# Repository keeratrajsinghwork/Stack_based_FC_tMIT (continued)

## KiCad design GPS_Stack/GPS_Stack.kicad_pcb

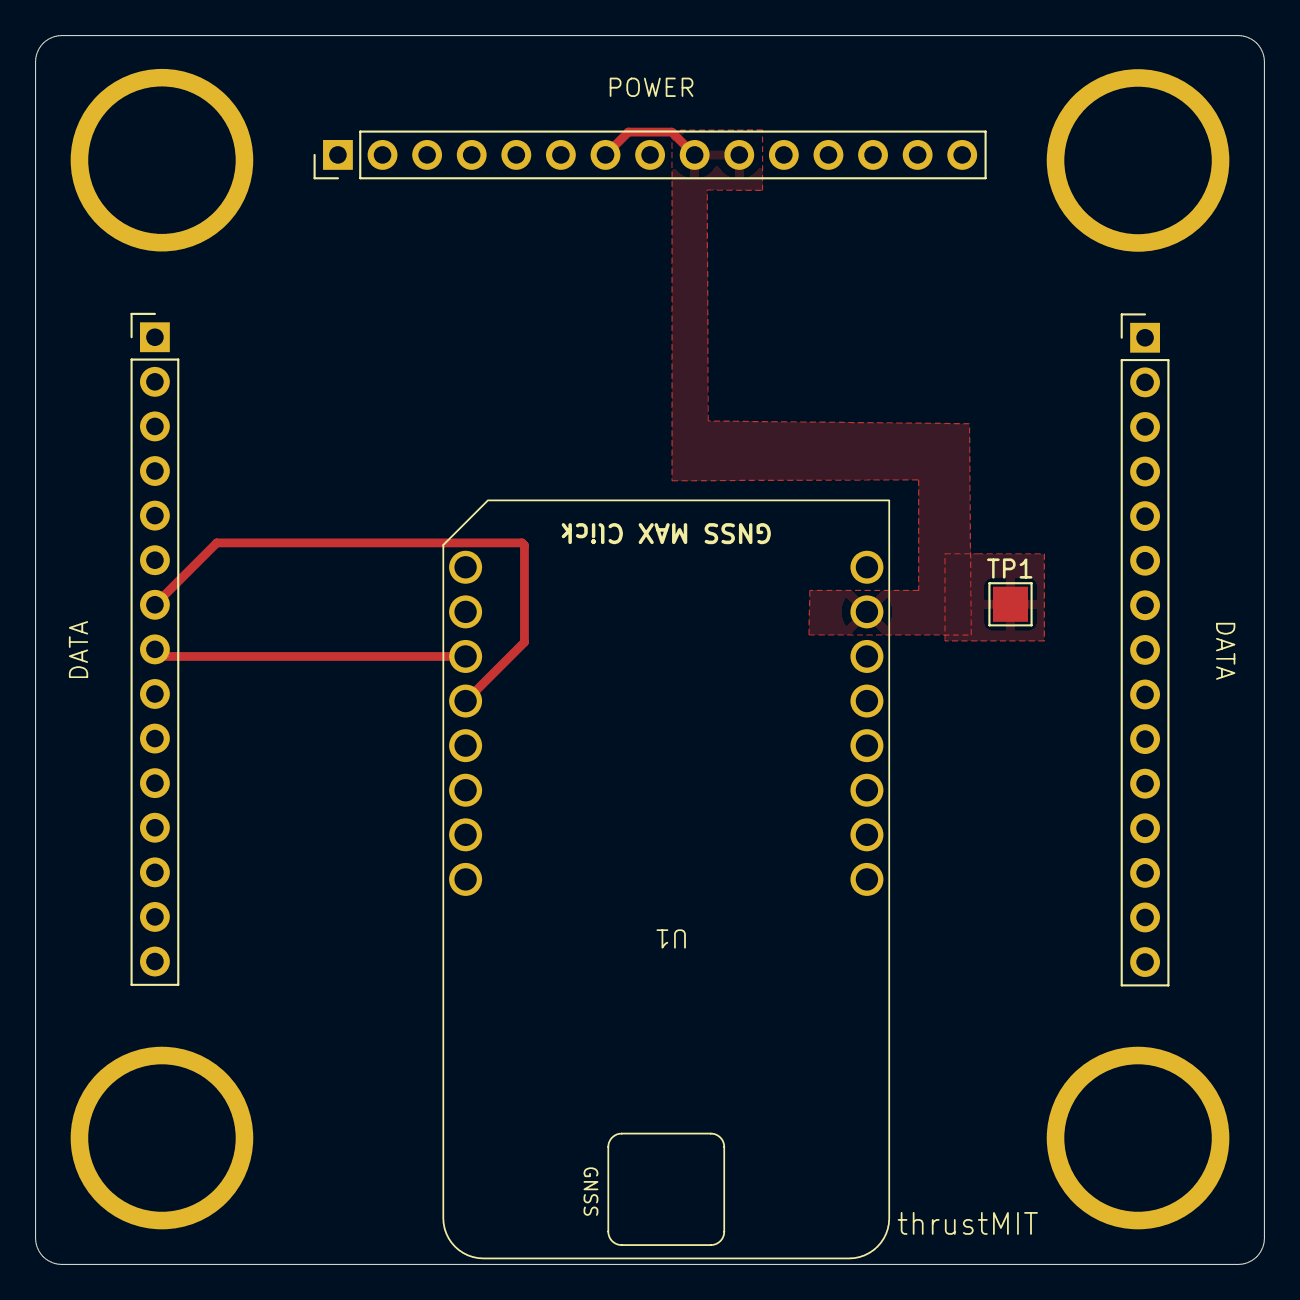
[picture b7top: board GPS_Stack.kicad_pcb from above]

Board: 2 copper layers, 70.0 x 70.0 mm, 3 parts (0 on the bottom side), 4 nets.

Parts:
TP1: TestPoint_Probe; TestPoint_Pad_2.0x2.0mm
U1: Mikroe_GNSS_MAX_CLICK_ThrustMIT
U2: FC_Stack_template

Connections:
3.3V: TP1.1, U1.2 (+3V3), U2.37, U2.39, U2.40
GND: U1.1 (GND), U1.9 (GND), U2.49 (1), U2.50 (1), U2.51 (1), U2.52 (1)
I2C1_SCL: U1.12 (SCL), U2.24
I2C1_SDA: U1.11 (SDA), U2.23

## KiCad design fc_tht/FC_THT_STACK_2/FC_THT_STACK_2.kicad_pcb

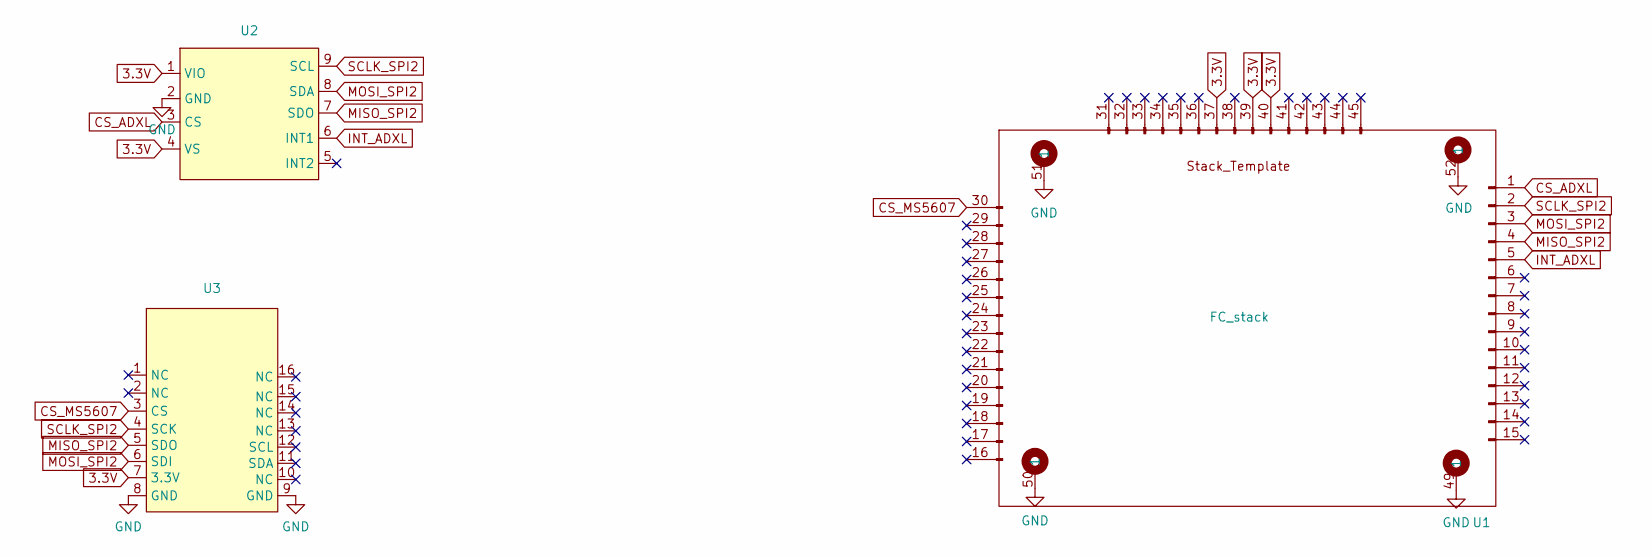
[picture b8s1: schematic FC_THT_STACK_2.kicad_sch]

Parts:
U1: FC_stack; FC_Stack_template
U2: ADXL375_EVAL
U3: Altitude_Click_2

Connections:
3.3V: U1.37, U1.39, U1.40, U2.1 (VIO), U2.4 (VS), U3.7 (3.3V)
CS_ADXL: U1.1, U2.3 (CS)
CS_MS5607: U1.30, U3.3 (CS)
GND: U1.49 (1), U1.50 (1), U1.51 (1), U1.52 (1), U2.2 (GND), U3.8 (GND), U3.9 (GND)
INT_ADXL: U1.5, U2.6 (INT1)
MISO_SPI2: U1.4, U2.7 (SDO), U3.5 (SDO)
MOSI_SPI2: U1.3, U2.8 (SDA), U3.6 (SDI)
SCLK_SPI2: U1.2, U2.9 (SCL), U3.4 (SCK)

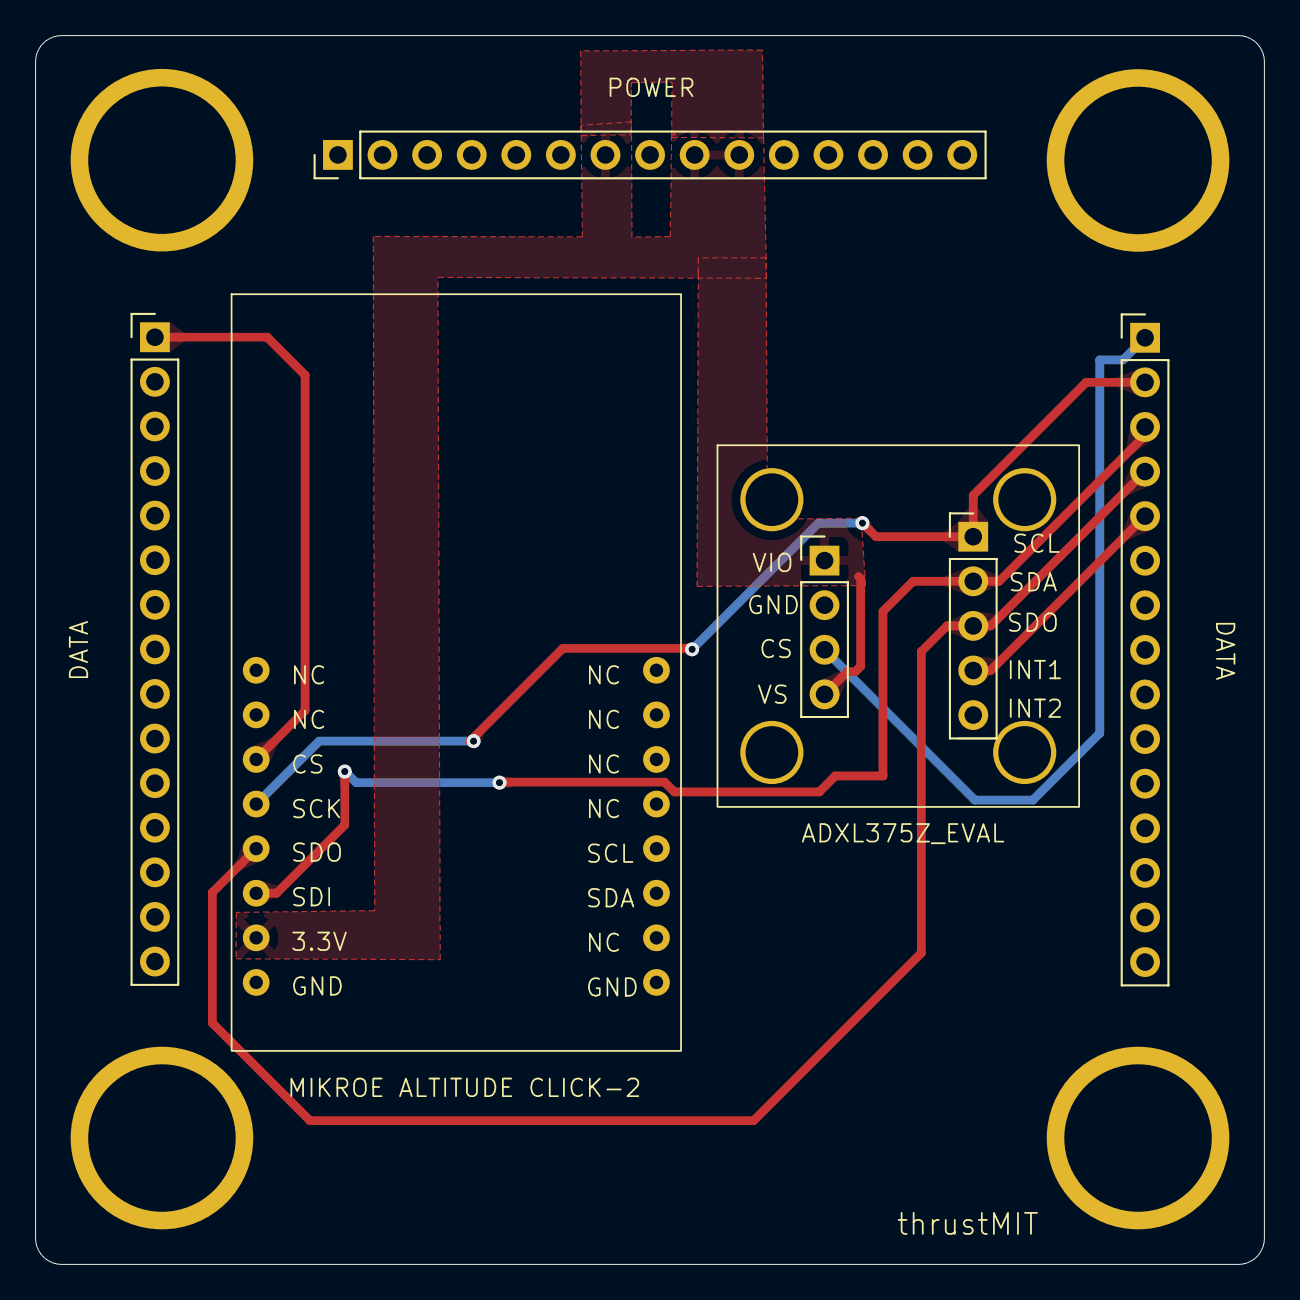
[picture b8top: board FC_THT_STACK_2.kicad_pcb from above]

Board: 2 copper layers, 70.0 x 70.0 mm, 3 parts (0 on the bottom side), 8 nets.
